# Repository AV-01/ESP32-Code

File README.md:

<!--  -->

<div align="center">
    <h1>
        av's homework machine
    </h1>
    <p>
        <strong>
            i hate doing homework, so i spent 40 hours avoiding it
        </strong>
    </p>
    <p>
        <a href="#features">Features</a> •
        <a href="#demo">Demo</a> •
        <a href="#pcb">PCB</a> •
        <a href="#cad-files">CAD</a> •
        <a href="#building--flashing-firmware">Firmware</a> •
        <a href="#usage">Usage</a>
    </p>

</div>

## What is this?

This machine does your homework! Well... there's a little bit more to it than that. First, it takes your handwriting and runs a custom Font Engine. So, once you give it your homework, it formulates a response, and then generates GCode and uploads it onto an SD Card. When this GCode is run on a 3d printer with a pen attachment, it will look exactly like you wrote it!

## How do you use it?

I designed this with an Ender 3 3d Printer in mind, since that's what I had. All you need is:
- SD Card
- A 3D Printer/Pen Plotter
- Some paper and a pen
And that's really it. There are some very cheap options out there, so anything you find will be fine!

## Why did you make this?

When I was in 3rd grade, I read a book called [The Homework Machine by Dan Gutman](https://www.goodreads.com/book/show/977597.The_Homework_Machine). Now, the moral of the story was that you should do your own homework. However, 9-year-old me didn't catch that deeper meaning, and instead thought: 

> woah i want a machine that does my homework :O

After Google failed to find me one, the idea became dormant for several years. Until like 2-3 months ago, I realized that my Ender 3 printer, which I bought for like $50, functioned exactly like a pen plotter! So, I spent a lot of time coding a font engine that can create GCode that looks exactly like your handwriting. Then, I crammed together a bunch of electronics to make a machine that automates a long pipeline to do your homework easy peasy!

## Features

- ESP32-powered
  - Configure settings via the webserver
  - Very Fast
- .96 inch display
- Battery Powered
- Rechargable
- Small size

Here's how it looks:        

## Demo

I'm working on making a demo, give me a sec...

## PCB

Images of schematics and PCB design are all under the [PCB folder](pcb/). I had a PCB ready and designed for this, but it came on June 20th, so I didn't create a CAD for it. It's better to use the individual components and a breadboard.

## CAD files

CAD files are under [`CAD/`](CAD/). I made this entirely in Fusion 360. I found models of all the electrical parts and rescaled them to match my actual parts, so the CAD isn't entirely accurate to real life!

## Building + flashing firmware

To build and flash the firmware, I used ArduinoIDE. I'm sure there's a way to use PlatformIO, but it'll probably be less straightforward. Go to ['Firmware'](firmware/) and send the [Webserver.ino](firmware/Webserver.ino) file to the ESP32. Then, in ArduinoIDE, press Ctrl+Shift+P and type "Upload LittleFS to Pico/ESP8266/ESP32", which will send everything from the [data folder](firmware/data/) to the microcontroller! 

## Usage

Everything is handled when you first launch. It'll turn into an Access Point, and you can connect directly to it and type in your WiFi credentials. After that, you can visit `"http://<IP>/settings"` to change anything, or visit the IP directly to use. All you need to do is upload your homework, press 3 buttons, and you're good to go! In data, it comes preinstalled with my handwriting, so you might want to change that.

## Magazine page

Check it out!!

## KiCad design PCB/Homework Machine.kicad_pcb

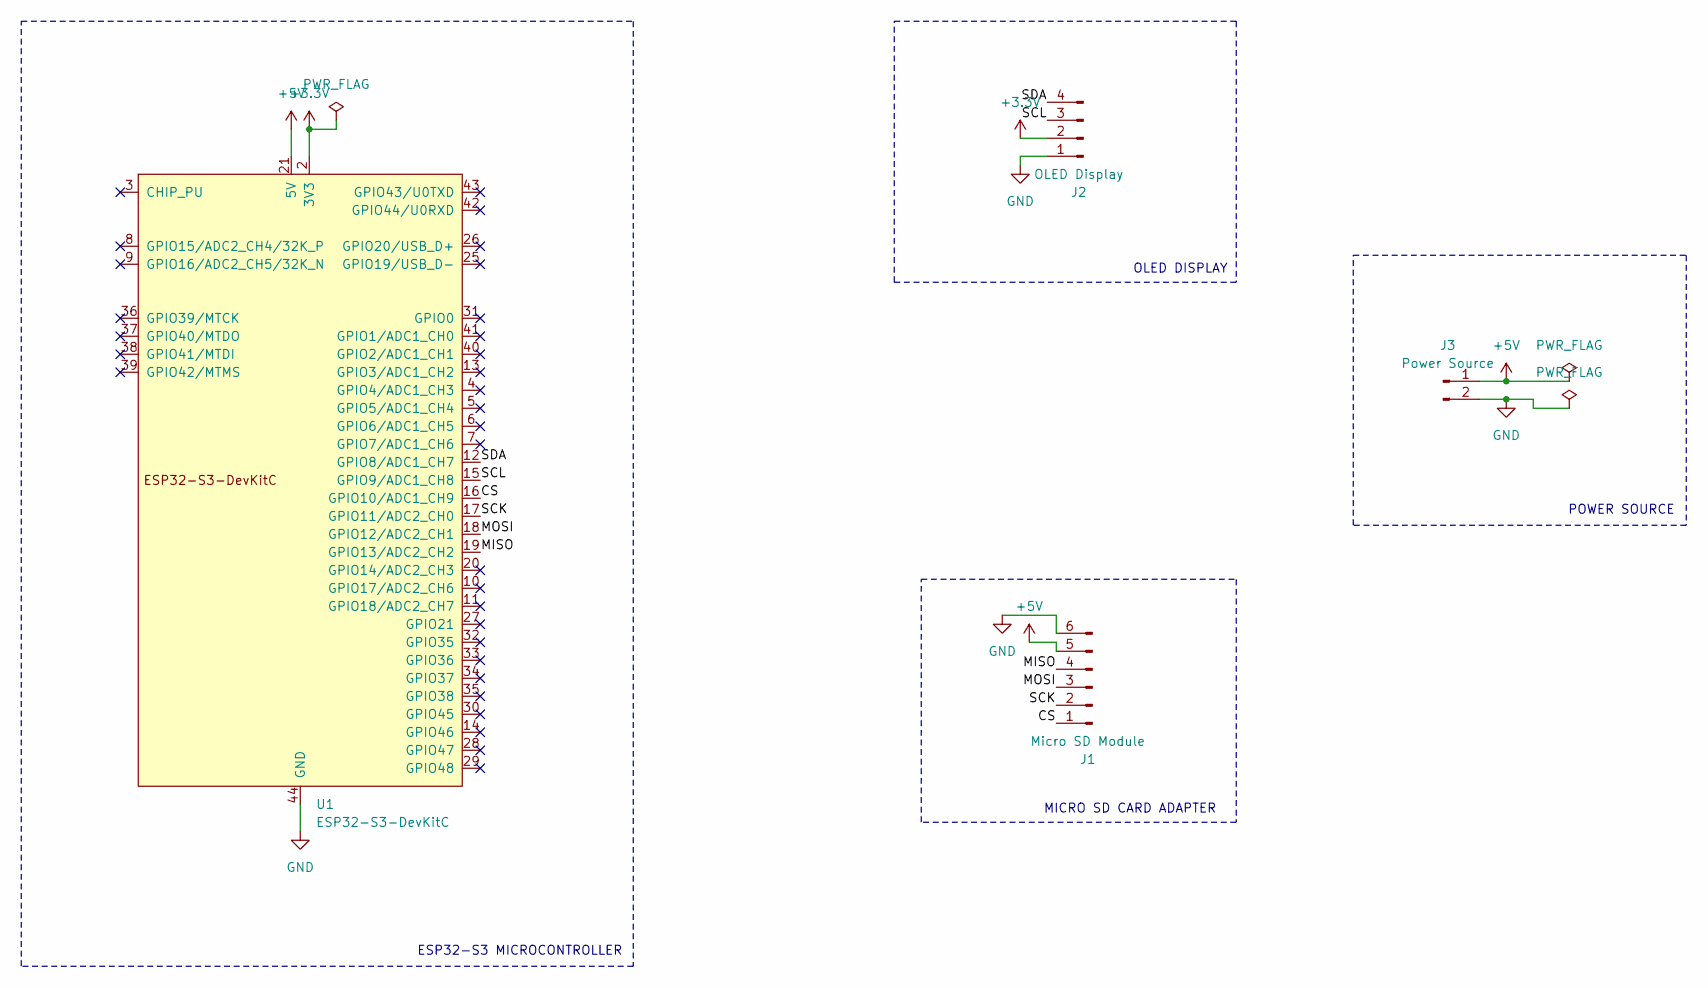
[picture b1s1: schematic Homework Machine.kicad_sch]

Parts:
J1: Micro SD Module; PinHeader_1x06_P2.54mm_Vertical
J2: OLED Display; PinHeader_1x04_P2.54mm_Vertical
J3: Power Source; PinHeader_1x02_P2.54mm_Vertical
U1: ESP32-S3-DevKitC; ESP32-S3-DevKitC-MODIFIED

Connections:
+3.3V: J2.2, U1.1 (3V3), U1.2 (3V3)
+5V: J1.5, J3.1, U1.21 (5V)
/CS: J1.1, U1.16 (GPIO10/ADC1_CH9)
/MISO: J1.4, U1.19 (GPIO13/ADC2_CH2)
/MOSI: J1.3, U1.18 (GPIO12/ADC2_CH1)
/SCK: J1.2, U1.17 (GPIO11/ADC2_CH0)
/SCL: J2.3, U1.15 (GPIO9/ADC1_CH8)
/SDA: J2.4, U1.12 (GPIO8/ADC1_CH7)
GND: J1.6, J2.1, J3.2, U1.22 (GND), U1.23 (GND), U1.24 (GND), U1.44 (GND)

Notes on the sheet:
MICRO SD CARD ADAPTER
OLED DISPLAY
ESP32-S3 MICROCONTROLLER
POWER SOURCE

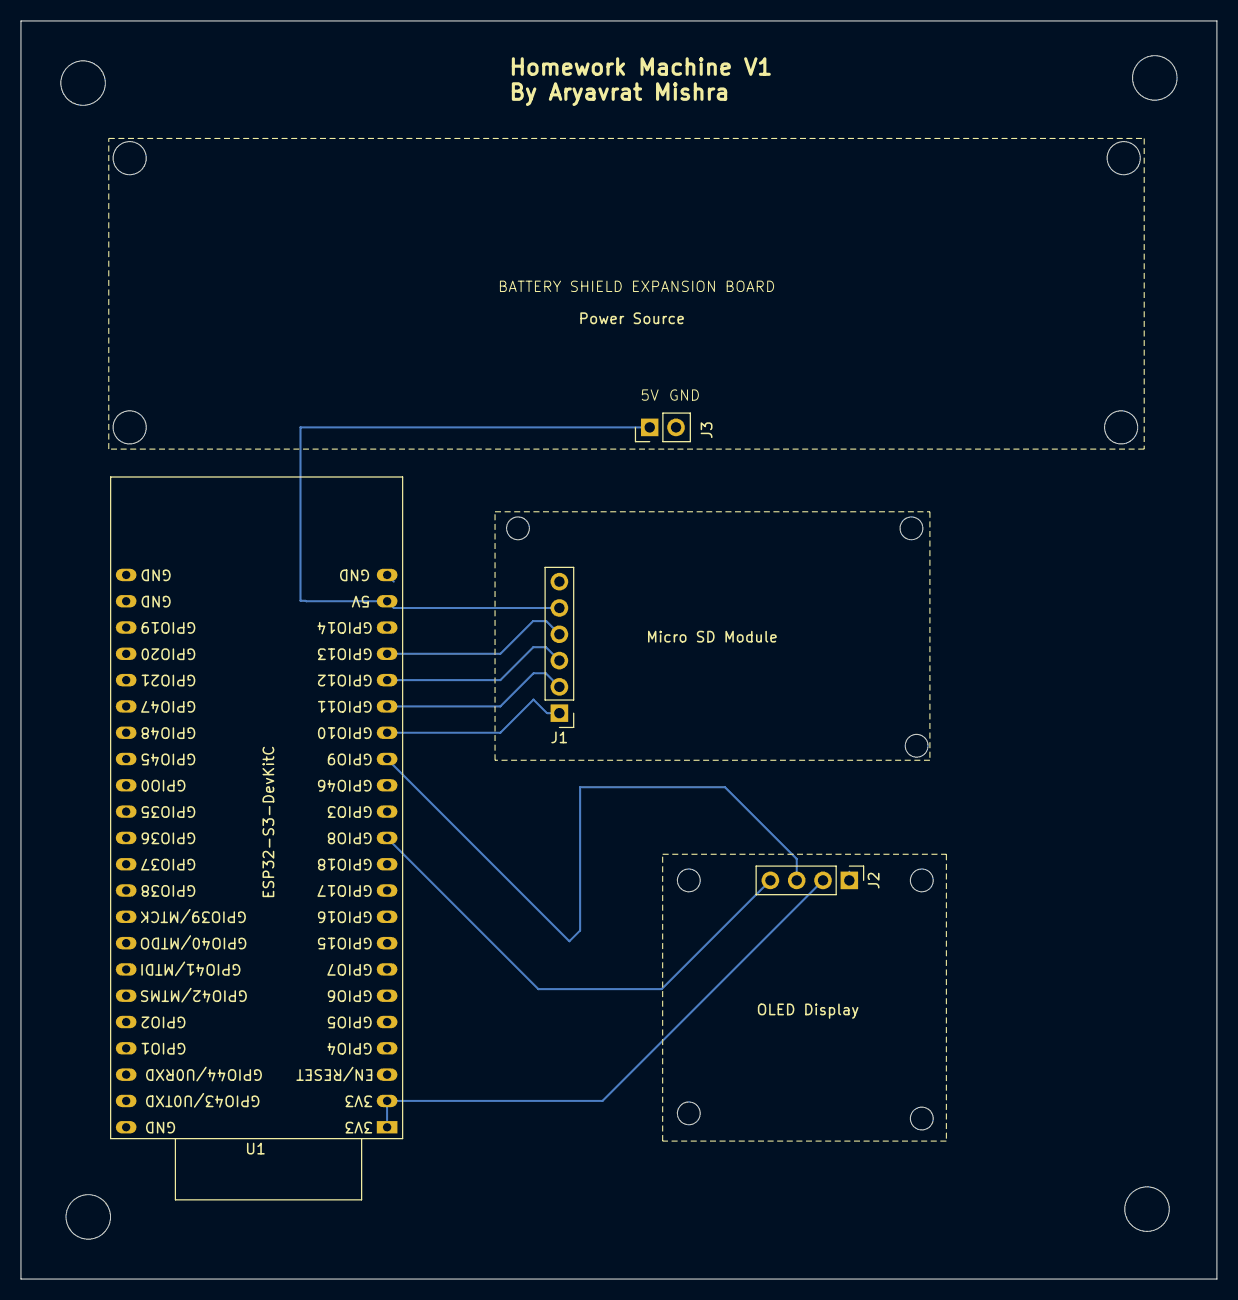
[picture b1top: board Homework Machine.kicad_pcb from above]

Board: 2 copper layers, 115.5 x 121.5 mm, 5 parts (0 on the bottom side), 9 nets.

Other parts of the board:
REF: MountingHole_3.2mm_M3

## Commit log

2026-05-07 init: create ESP32 webserver with dummy html page
2026-05-09 feat: AI Backend Config & ESP32 Persistent Memory
2026-05-10 refactor: add API Key endpoint
    Expose a /get-api-key endpoint that returns the stored API key as JSON (uses preferences.getString and checks hasWifi and non-empty key; responds 400 on failure). Update index.html to fetch the API k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
2026-05-11 feat: enable multi-file image upload
    Users can now upload multiple images, which will be converted into Base 64 and sent to Gemini API for homework requests
2026-05-11 feat: display and QR Code features for setup
    Using display, user can see QR Codes and URLs for either "setup.html" or "main.html". Basically, on setup, the ESP32 determines if it has WiFi access, and displays appropriate QR Code.
2026-05-12 feat: display instructions on screen
    Added instructions on screen so that first-time users can quickly understand how to use device. Refactored old code and comments
2026-05-13 BROKEN: 1.0.0 font_engine.js
2026-05-13 fix: font_engine.js V1.0.1 fixed
2026-05-16 feat: V1.0.0, SD Card WebServer
2026-05-17 refactor: delete files, create settings update
2026-05-18 feat: create SD card writing & update settings upload
2026-05-18 fix: settings update feature FIXED
2026-06-14 BROKEN: fixing upload-file to handle larger files, knicks in five
2026-06-21 feat: added files and better README.md
2026-06-21 feat: done!
